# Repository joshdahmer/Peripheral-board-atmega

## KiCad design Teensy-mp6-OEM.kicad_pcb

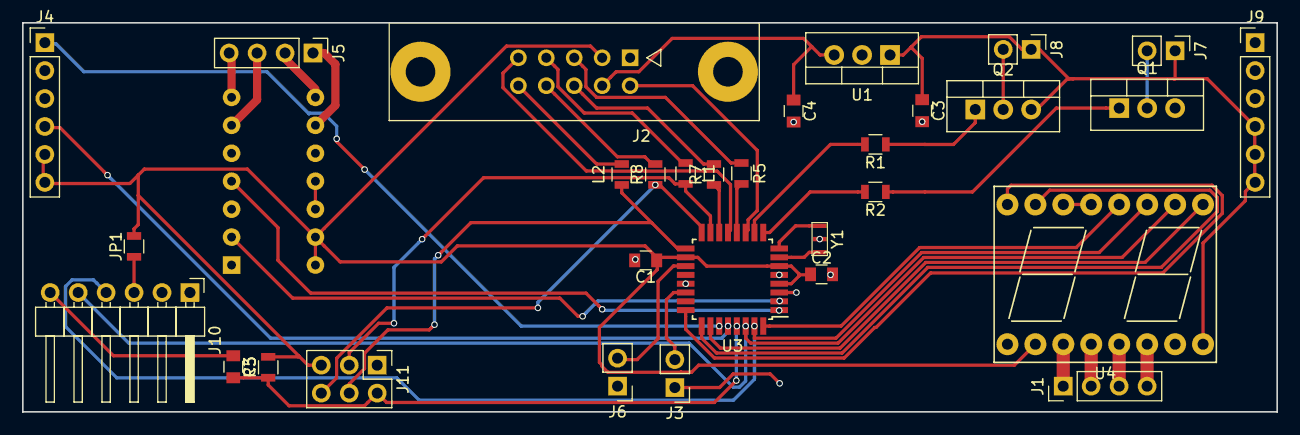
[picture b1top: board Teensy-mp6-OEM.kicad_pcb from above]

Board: 2 copper layers, 114.0 x 35.4 mm, 32 parts (1 on the bottom side), 49 nets.

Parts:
C1, C2, C4, C5: 0.1uF; C_0805
C3: 0.33uF; C_0805
J1: STEPPERMOTOR; Pin_Header_Straight_1x04_Pitch2.54mm
J2: CONN_02X05; he10-10d
J3: ENDSTOP2; Pin_Header_Straight_1x02_Pitch2.54mm
J4: CONN_LEFT; Pin_Header_Straight_1x06_Pitch2.54mm
J5: PUMP; Pin_Header_Straight_1x04_Pitch2.54mm
J6: ENDSTOP1; Pin_Header_Straight_1x02_Pitch2.54mm
J7: LED1; Pin_Header_Straight_1x02_Pitch2.54mm
J8: LED2; Pin_Header_Straight_1x02_Pitch2.54mm
J9: CONN_RIGHT; Pin_Header_Straight_1x06_Pitch2.54mm
J10: CONN_ARDUINO; Pin_Header_Angled_1x06_Pitch2.54mm
J11: CONN_ISP; Pin_Header_Straight_2x03_Pitch2.54mm
JP1: Jumper; R_0805
L1, L2: Ferrite_Bead; L_0805
Q1: MOSFET1; TO-220_Vertical
Q2: MOSFET2; TO-220_Vertical
R1, R2: 165; R_0805
R3: 10k; R_0805
R5, R7, R8: 50; R_0805
U1: LM7805CT; TO-220_Vertical
U2: mp6-OEM; DIP-14_W7.62mm
U3: ATMEGA328P-AU; TQFP-32_7x7mm_Pitch0.8mm
U4: A4988-Stepper-Controller; DA04
Y1: RESONATOR; CSTCE_G15C

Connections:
1A: J1.2, U4.12
1B: J1.1, U4.11
2A: J1.3, U4.13
2B: J1.4, U4.14
+3.3V: C1.1, C2.1, J2.3, J4.5, J4.6, J11.5, JP1.2, R3.2, U2.13, U2.14, U3.4, U3.6, U3.18, U4.10
+3.3V_USB: J10.3, JP1.1
+5V: C4.1, J2.4, U1.3
+12V: C3.1, J7.1, J8.1, J9.4, J9.5, J9.6, Q2.3, U1.1, U4.16
AMPLTUDE: U2.4, U3.1
CS_ADC: R7.1, U3.14
CS_POT: R5.2, U3.12
DIR: U3.24, U4.8
DRAIN_1: J7.2, Q1.2
DRAIN_2: J8.2, Q2.2
ENABLE: U3.26, U4.1
END_STOP_1: J6.2, U3.19
END_STOP_2: J3.2, U3.22
FREQ_PIN: U2.2, U3.2
GND: C1.2, C2.2, C3.2, C4.2, J2.1, J3.1, J4.2, J4.3, J6.1, J9.1, J9.2, J9.3, J10.1, J11.1, Q1.3, U1.2, U2.1, U2.5, U2.10, U3.3, U3.5, U3.21, U4.9, U4.15, Y1.2
LED_GATE_1: R2.2, U3.9
LED_GATE_2: R1.2, U3.10
MISO: J11.6, R8.1, U3.16
MONITOR: J2.2, U3.11
MOSI: J11.3, L1.2, U3.15
MS1/RX: J10.5, U3.30, U4.2
MS2/TX: J10.4, U3.31, U4.3
MS3: U3.32, U4.4
unnamed: C5.1, J10.6
unnamed: J2.5, R5.1
unnamed: J2.6, R7.2
unnamed: J2.7, L1.1
unnamed: J2.8, R8.2
unnamed: J2.10, L2.2
unnamed: Q1.1, R2.1
unnamed: Q2.1, R1.1
unnamed: U2.11, U2.12
unnamed: U3.7, Y1.3
unnamed: U3.8, Y1.1
unnamed: U4.5, U4.6
P1+: J5.3, U2.6
P1-: J5.4, U2.7
P2+: J5.1, U2.9
P2-: J5.2, U2.8
RST: C5.2, J11.2, R3.1, U3.29
SCK: J11.4, L2.1, U3.17
SCL: J4.4, U3.28
SDA: J4.1, U3.27
SHUTTER: J2.9, U3.13
STEP: U3.25, U4.7

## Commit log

2017-07-12 Fixed broken 12V connection and mp6 pin orientation
